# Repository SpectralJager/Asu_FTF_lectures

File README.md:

Великие труды прошедших этот путь

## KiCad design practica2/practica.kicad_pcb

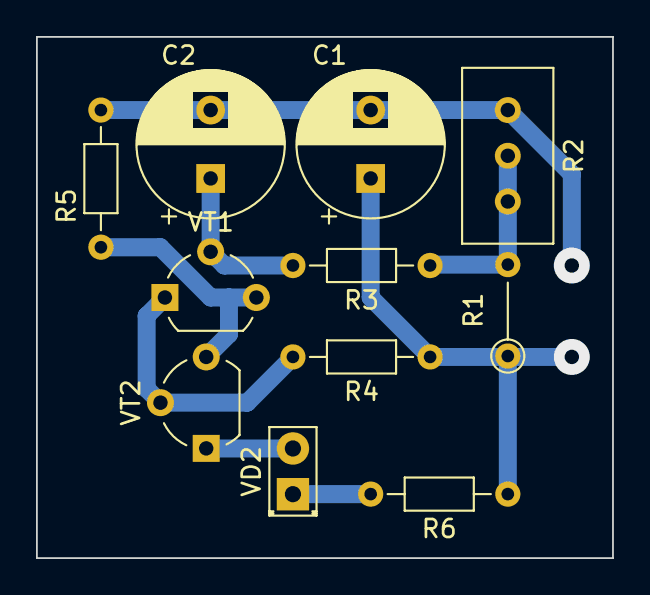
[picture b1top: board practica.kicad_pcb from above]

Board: 2 copper layers, 32.0 x 29.0 mm, 11 parts (0 on the bottom side), 8 nets.

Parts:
C1, C2: 10u; CP_Radial_D8.0mm_P3.80mm
R1: GL5516; R_Axial_DIN0204_L3.6mm_D1.6mm_P5.08mm_Vertical
R2: 10k; Potentiometer_Bourns_3296W_Vertical
R3: 4,7k; R_Axial_DIN0204_L3.6mm_D1.6mm_P7.62mm_Horizontal
R4: 3,3k; R_Axial_DIN0204_L3.6mm_D1.6mm_P7.62mm_Horizontal
R5, R6: 33; R_Axial_DIN0204_L3.6mm_D1.6mm_P7.62mm_Horizontal
VD2: LED; LED_D2.0mm_W4.8mm_H2.5mm_FlatTop
VT1, VT2: BC549; TO-92_Wide

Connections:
+12V: C1.1, R1.1, R4.1, R6.1
GND: C1.2, C2.2, R2.3, R5.2
unnamed: R1.2, R2.1, R2.2, R3.1
unnamed: VD2.2 (A), VT2.1 (C)
unnamed: R6.2, VD2.1 (K)
unnamed: C2.1, R3.2, VT1.2 (B)
unnamed: R4.2, VT1.1 (C), VT2.2 (B)
unnamed: R5.1, VT1.3 (E), VT2.3 (E)

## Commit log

2019-09-05 calc_1
2019-09-05 calc_fix
2019-09-05 calcfix1
2019-09-10 eng1
2019-09-10 fiz2
2019-09-10 font change
2019-09-11 lin 2
2019-09-11 lin 2 and fixes
2019-09-12 calc2
2019-09-16 16.09 inf and eng_graph
2019-09-17 физр 3
2019-09-17 shit programming les
2019-09-18 lin_alg 3
2019-09-21 calc3
2019-09-23 23 09
2019-09-25 lim 4
2019-09-27 calc4
2019-09-27 eng_graph added img
2019-09-30 inf and eng 30.09
2019-10-01 физра
2019-10-08 0710
2019-10-10 repair
2019-10-10 repeir
2019-10-15 eng 1410
2019-10-29 2810
2021-10-06 asm_lab2_1
    asm code done
2021-10-18 elect_lab1
2021-10-20 elect_lab2
2021-10-22 elect_lab3
2021-11-01 elect_lab4,5,6
2021-12-05 Auto stash before merge of "master" and "origin/master"
2023-02-25 Auto stash before rebase of "origin/master"
2023-11-02 Bump golang.org/x/image from 0.5.0 to 0.10.0 in /graphics
    Bumps [golang.org/x/image](https://github.com/golang/image) from 0.5.0 to 0.10.0.
    - [Commits](https://github.com/golang/image/compare/v0.5.0...v0.10.0)
    ---
    updated-dependencies:
    - dependency-name: golang.org/x/image
    dependency-type: direct:production
2024-06-02 done
